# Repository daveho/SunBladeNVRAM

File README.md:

# M48T59Y replacement module

I designed a replacement for the M48T59Y-70PC1 NVRAM/RTC module used in some
Sun workstations, such as the Sun Blade 150:

All of the project files, including the KiCad project, assembly
instructions, and a design for an Arduino-based tester/programmer, are here:

<https://github.com/daveho/RandomStuff/tree/master/Episode0d>

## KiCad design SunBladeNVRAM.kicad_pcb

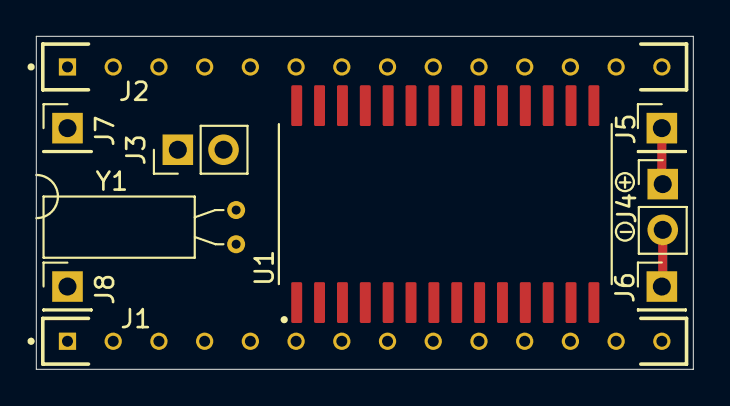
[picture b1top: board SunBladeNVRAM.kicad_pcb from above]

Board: 2 copper layers, 36.5 x 18.5 mm, 10 parts (0 on the bottom side), 32 nets.

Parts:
J1, J2: Conn_01x14_Pin; SAMTEC_BBL-114-T-E
J3, J4: Conn_01x02_Pin; PinHeader_1x02_P2.54mm_Vertical
J5, J6, J7, J8: Conn_01x01_Pin; PinHeader_1x01_P2.54mm_Vertical
U1: M48T59Y-70MH1; M48T59Y-MH
Y1: 32.768 kHz; Crystal_C38-LF_D3.0mm_L8.0mm_Horizontal

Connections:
unnamed: J1.1, U1.1 (-RST)
unnamed: J1.2, U1.2 (A12)
unnamed: J1.3, U1.3 (A7)
unnamed: J1.4, U1.4 (A6)
unnamed: J1.5, U1.5 (A5)
unnamed: J1.6, U1.6 (A4)
unnamed: J1.7, U1.7 (A3)
unnamed: J1.8, U1.8 (A2)
unnamed: J1.9, U1.9 (A1)
unnamed: J1.10, U1.10 (A0)
unnamed: J1.11, U1.11 (DQ0)
unnamed: J1.12, U1.12 (DQ1)
unnamed: J1.13, U1.13 (DQ2)
unnamed: J1.14, U1.14 (VSS)
unnamed: J2.1, U1.28 (VCC)
unnamed: J2.2, U1.27 (-W)
unnamed: J2.3, U1.26 (-IRQ/FT)
unnamed: J2.4, U1.25 (A8)
unnamed: J2.5, U1.24 (A9)
unnamed: J2.6, U1.23 (A11)
unnamed: J2.7, U1.22 (-G)
unnamed: J2.8, U1.21 (A10)
unnamed: J2.9, U1.20 (-E)
unnamed: J2.10, U1.19 (DQ7)
unnamed: J2.11, U1.18 (DQ6)
unnamed: J2.12, U1.17 (DQ5)
unnamed: J2.13, U1.16 (DQ4)
unnamed: J2.14, U1.15 (DQ3)
unnamed: J3.1, Y1.1
unnamed: J3.2, Y1.2
unnamed: J4.1, J5.1
unnamed: J4.2, J6.1

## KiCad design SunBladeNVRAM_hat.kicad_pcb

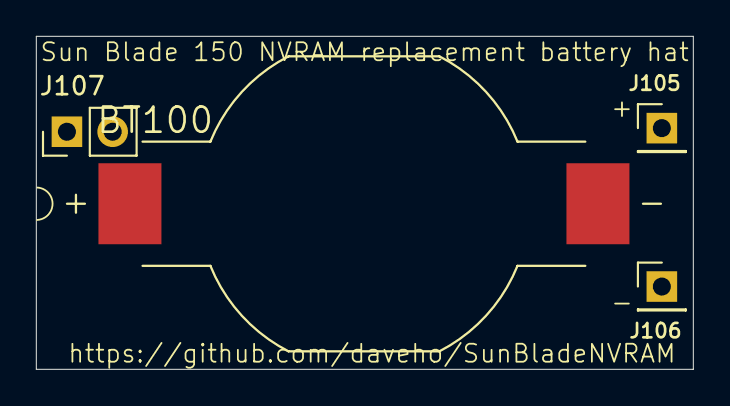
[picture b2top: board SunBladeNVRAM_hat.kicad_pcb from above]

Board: 2 copper layers, 36.5 x 18.5 mm, 4 parts (0 on the bottom side), 2 nets.

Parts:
BT100: BU1632SM-JJ-GTR; BAT_BU1632SM-JJ-GTR
J105, J106: Conn_01x01_Pin; PinHeader_1x01_P2.54mm_Vertical
J107: Conn_01x02_Pin; PinHeader_1x02_P2.54mm_Vertical

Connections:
unnamed: BT100.+, J105.1
unnamed: BT100.-, J106.1

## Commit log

2024-11-17 footprint for CR1632 battery
    Source:
    https://www.snapeda.com/parts/BU1632SM-JJ-GTR/Memory%20Protection%20Devices/view-part/
2024-11-17 created schematic
2024-11-17 assign footprints
2024-11-17 add project footprint lib for battery holder
2024-11-17 fix watch crystal footprint assignment
2024-11-17 put battery on stacked "hat" PCB
    There's not enough room for all of the components
    otherwise if we want to fit in the area of a standard
    DIP28 part.
2024-11-17 assign footprints for single pin headers
2024-11-17 initial component placements for module PCB
2024-11-17 explicitly mark unconnected pins
2024-11-17 routed connections (seems ok?)
2024-11-17 move J2 silkscreen so it's on the board
2024-11-17 minor placement tweak
2024-11-17 PCB for battery "hat"
2024-11-17 mark +/- pins for battery connection to M48T59Y
2024-12-06 connector positions
2024-12-06 correct M48T59Y-MH footprint
2024-12-06 use correct M48T59Y-MH footprint
    Changed pin headers to be surface mount, meaning the
    pads can be on the bottom and so not interfere with the
    M49T59Y.
    Bottom PCB needs to be a bit larger, and the top
    (battery hat) PCB also needed a minor redesign.
    Still need to route the connections.
2024-12-10 improved 1x14 header, M48T59Y-MH footprints
    The 1x14 header footprint is for round (machine pin)
    headers, which is what we want to use. The through holes
    are much more compact than the footprint for normal
    square headers.
    The M48T59Y footprint is made slightly more compact.
    It should still allow plenty of room to solder on the
2024-12-10 move designators for J1 and J2
2024-12-10 fix pin numbers on SAMTEC 1x14 footprint
    Also, remove some of the silkscreen on the SAMTEC
    1x14 headers so that it doesn't overlap the M48T59Y
    footprint.
2024-12-10 move 1x14 header designators again
2024-12-10 routed all traces, a few minor tweaks
    Ready to fab?
2024-12-31 working on Arduino test program
2024-12-31 M48T59Y control, RNG for data tests
2024-12-31 move main KiCAD project to subdirectory
2024-12-31 move more files into subdirectory
2024-12-31 one more file moved to subdirectory
2024-12-31 schematic for test circuit
2024-12-31 a few minor corrections to the test circuit
2025-01-01 implement reads and writes
    It turns out that not all of the pins of PORTC are
    available on the Arduino Nano, so changed the test
    circuit and test program to use the low 3 bits of
    PORTB to interface with the high nybble of the
    data bus.
    I can successfully write to and read from two bytes
2025-01-01 add pull-ups to -E, -G, and -W signals
    The idea is to try to avoid any spurious writes to
    the M48T59Y on power-up or reset.
2025-01-01 print verification mismatch addresses
2025-01-02 address 0x1FEF doesn't verify consistently
    Not sure why yet.
2025-01-02 add GO and LOG buttons
    pressing GO starts the tests
    if LOG is held down when GO is pressed, verification
    errors are logged
2025-01-02 add GO and LOG pushbuttons
2025-01-03 fix typo
2025-01-03 test setting time and date
    seems to work?
2025-01-04 major refactoring
    Was trying to figure out why all tests will failing
    with every M48T59Y, but the problem actually seems
    to be that I switched the Arduino to a USB hub which
    was not producing a sufficiently high VCC! Plugging
    the Arduino directly into one of the computer's front
    panel USB ports seems to have resolved the issue.
2025-01-06 just make this a link to the actual repo
2026-03-08 link to correct site

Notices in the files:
SunBladeNVRAM.kicad_pcb:
(c) 2024, daveho hacks
